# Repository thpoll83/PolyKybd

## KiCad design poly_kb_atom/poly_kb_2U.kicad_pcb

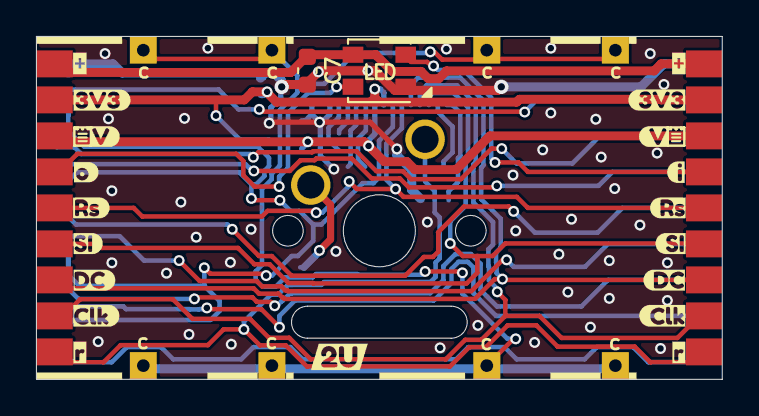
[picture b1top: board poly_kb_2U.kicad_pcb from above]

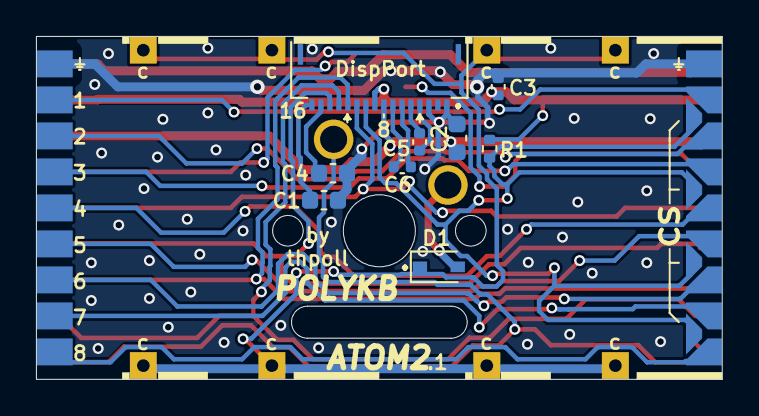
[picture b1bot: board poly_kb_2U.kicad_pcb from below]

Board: 2 copper layers, 38.1 x 19.0 mm, 43 parts (11 on the bottom side), 27 nets.

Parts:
C1, C2: 2.2uF; C_0603_1608Metric
C3, C5, C6: 1uF; C_0402_1005Metric
C4: 4.7uF; C_0603_1608Metric
C7: 100nF; C_0603_1608Metric
D1: D_Small; D_SOD-323Ext
J1: Conn_01x16; FPC_16_JUSHUO_AFC05_S16FIA_00
J2, J2#2: North; TestPoin_1.5x1.5mm_Drill0.7mm
J3: WestFront; AtomConnect2
J4: EastFront; AtomConnect2
J5: WestBack; AtomConnectCS
J6: EastBack; AtomConnect2
J7, J7#2: South; TestPoin_1.5x1.5mm_Drill0.7mm
J8, J10: North2; TestPoin_1.5x1.5mm_Drill0.7mm
J9, J9#2: South2; TestPoin_1.5x1.5mm_Drill0.7mm
LED1: WS2812B-Mini
R1: 1M; R_0402_1005Metric
SW1: SW_Push; SW_Cherry_MX_1.00u_PCB_NoSilk
kibuzzard-61EFA8F1: G***; kibuzzard-61EFA8F1
kibuzzard-61EFAA6D: G***; kibuzzard-61EFAA6D
kibuzzard-61EFABBF: G***; kibuzzard-61EFABBF
kibuzzard-61EFACF9: G***; kibuzzard-61EFACF9
kibuzzard-61EFBE2C: G***; kibuzzard-61EFBE2C
kibuzzard-61EFBE3D: G***; kibuzzard-61EFBE3D
kibuzzard-61EFBE21: G***; kibuzzard-61EFBE21
kibuzzard-61EFBE87: G***; kibuzzard-61EFBE87
kibuzzard-61EFD7F9: G***; kibuzzard-61EFD7F9
kibuzzard-61EFD863: G***; kibuzzard-61EFD863
kibuzzard-61EFD879: G***; kibuzzard-61EFD879
kibuzzard-61EFD908, kibuzzard-61EFD908#2: G***; kibuzzard-61EFD908
kibuzzard-61EFD947, kibuzzard-61EFD947#2: G***; kibuzzard-61EFD947
kibuzzard-61EFDAA0: G***; kibuzzard-61EFDAA0
kibuzzard-61EFDAC6: G***; kibuzzard-61EFDAC6
kibuzzard-61EFDAEE: G***; kibuzzard-61EFDAEE
kibuzzard-620831A4: G***; kibuzzard-620831A4

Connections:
/Keyboard/sheet605ED2EB/3V3: C3.1, J1.9, J3.2, J4.2, R1.1
/Keyboard/sheet605ED2EB/4V2: C2.1, J1.8, J3.3, J4.3
/Keyboard/sheet605ED2EB/5V: C7.1, J3.1, J4.1, LED1.1 (VDD)
/Keyboard/sheet605ED2EB/CS: J1.10, J5.10, R1.2
/Keyboard/sheet605ED2EB/D-C: J1.12, J3.7, J4.7
/Keyboard/sheet605ED2EB/GND: C1.2, C2.2, C3.2, C4.2, C7.2, J1.1, J1.3, J5.1, J6.1, LED1.3 (VSS)
/Keyboard/sheet605ED2EB/KeyCol: D1.1 (K), J2.1, J2#2.1, J7.1, J7#2.1, J8.1, J9.1, J9#2.1, J10.1
/Keyboard/sheet605ED2EB/KeyRow: J3.9, J4.9, SW1.1
/Keyboard/sheet605ED2EB/LED_DIN: J3.4, J4.4, LED1.2 (DOUT), LED1.4 (DIN)
/Keyboard/sheet605ED2EB/RESET: J1.11, J3.5, J4.5
/Keyboard/sheet605ED2EB/SCLK: J1.13, J3.8, J4.8
/Keyboard/sheet605ED2EB/SDIN: J1.14, J3.6, J4.6
CS1: J5.2, J6.2
CS2: J5.3, J6.3
CS3: J5.4, J6.4
CS4: J5.5, J6.5
CS5: J5.6, J6.6
CS6: J5.7, J6.7
CS7: J5.8, J6.8
CS8: J5.9, J6.9
unnamed: C1.1, J1.16
unnamed: C4.1, J1.15
unnamed: C5.1, J1.4
unnamed: C5.2, J1.5
unnamed: C6.1, J1.6
unnamed: C6.2, J1.7
unnamed: D1.2 (A), SW1.2

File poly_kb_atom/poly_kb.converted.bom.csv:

Designator,Quantity,Value,Footprint,LCSC Part #,Comment
"C1, C2",2,2.2uF,C_0603_1608Metric,C23630," Unpolarized capacitor, small symbol"
"C3, C5, C6",3,1uF,C_0402_1005Metric,C52923," Unpolarized capacitor, small symbol"
C4,1,4.7uF,C_0603_1608Metric,C19666," Unpolarized capacitor, small symbol"
D1,1,D_Small,D_SOD-323F,C2826370," Diode, small symbol"
J1,1,Conn_01x16,FPC_16_JUSHUO_AFC05_S16FIA_00,C561388," Generic connector, single row, 01x16, script generated (kicad-library-utils/schlib/autogen/connector/)"
J2,1,North,TestPoin_1.5x1.5mm_Drill0.7mm,," Generic connector, single row, 01x01, script generated (kicad-library-utils/schlib/autogen/connector/)"
J3,1,WestFront,AtomConnect2,," Generic connector, single row, 01x09, script generated (kicad-library-utils/schlib/autogen/connector/)"
J4,1,EastFront,AtomConnect2,," Generic connector, single row, 01x09, script generated (kicad-library-utils/schlib/autogen/connector/)"
J5,1,WestBack,AtomConnectCS,," Generic connector, single row, 01x10, script generated (kicad-library-utils/schlib/autogen/connector/)"
J6,1,EastBack,AtomConnect2,," Generic connector, single row, 01x09, script generated (kicad-library-utils/schlib/autogen/connector/)"
J7,1,South,TestPoin_1.5x1.5mm_Drill0.7mm,," Generic connector, single row, 01x01, script generated (kicad-library-utils/schlib/autogen/connector/)"
J8,1,North2,TestPoin_1.5x1.5mm_Drill0.7mm,," Generic connector, single row, 01x01, script generated (kicad-library-utils/schlib/autogen/connector/)"
J9,1,South2,TestPoin_1.5x1.5mm_Drill0.7mm,," Generic connector, single row, 01x01, script generated (kicad-library-utils/schlib/autogen/connector/)"
LED1,1,WS2812B-Mini,WS2812B-Mini,C527089, RGB LED with integrated controller
SW1,1,SW_Push,SW_Cherry_MX_1.00u_PCB_NoSilk,," Push button switch, generic, two pins"
